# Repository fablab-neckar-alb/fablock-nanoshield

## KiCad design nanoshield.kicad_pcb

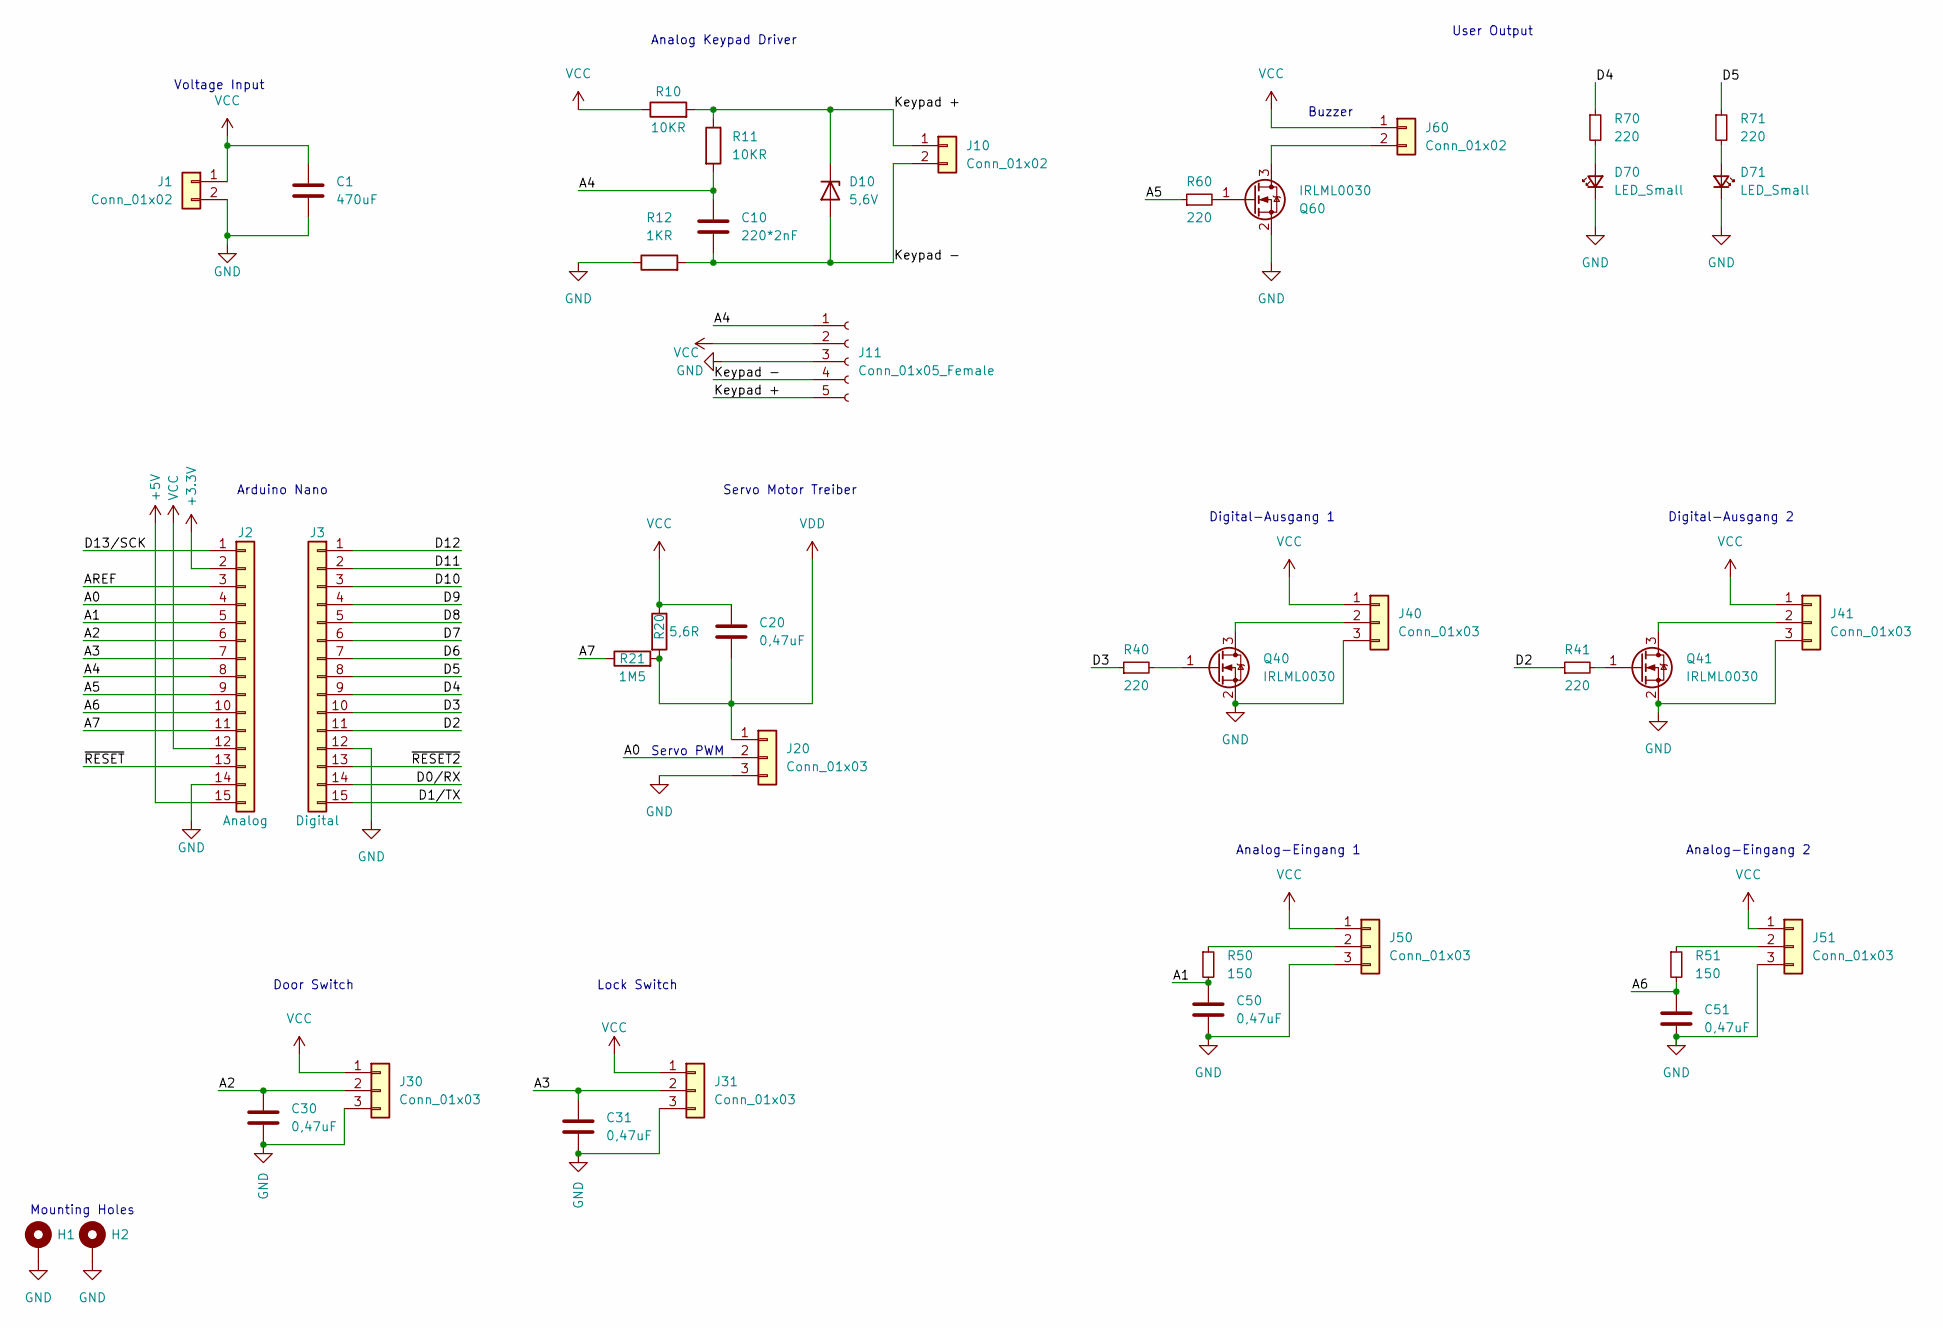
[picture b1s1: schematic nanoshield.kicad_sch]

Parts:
C1: 470uF; CP_Radial_D10.0mm_P5.00mm
C10: 220*2nF; C_Rect_L7.2mm_W2.5mm_P5.00mm_FKS2_FKP2_MKS2_MKP2
C20, C30, C31, C50, C51: 0,47uF; C_Rect_L7.2mm_W3.0mm_P5.00mm_FKS2_FKP2_MKS2_MKP2
D10: 5,6V; D_DO-15_P12.70mm_Horizontal
D70, D71: LED_Small; LED_Rectangular_W3.0mm_H2.0mm
H1: H1; MountingHole_3.5mm_Pad
H2: H2; MountingHole_3.5mm_Pad
J1, J10, J60: Conn_01x02; PhoenixContact_MCV_1,5_2-G-3.5_1x02_P3.50mm_Vertical
J2: Analog; PinHeader_1x15_P2.54mm_Vertical
J3: Digital; PinHeader_1x15_P2.54mm_Vertical
J11: Conn_01x05_Female; PinSocket_1x05_P2.54mm_Vertical
J20, J30, J31, J40, J41, J50, J51: Conn_01x03; PhoenixContact_MCV_1,5_3-G-3.5_1x03_P3.50mm_Vertical
Q40, Q41, Q60: IRLML0030; SOT-23
R10, R11: 10KR; R_Axial_DIN0309_L9.0mm_D3.2mm_P12.70mm_Horizontal
R12: 1KR; R_Axial_DIN0309_L9.0mm_D3.2mm_P12.70mm_Horizontal
R20: 5,6R; R_Axial_DIN0411_L9.9mm_D3.6mm_P20.32mm_Horizontal
R21: 1M5; R_Axial_DIN0309_L9.0mm_D3.2mm_P12.70mm_Horizontal
R40, R41, R60, R70, R71: 220; R_Axial_DIN0309_L9.0mm_D3.2mm_P12.70mm_Horizontal
R50, R51: 150; R_Axial_DIN0309_L9.0mm_D3.2mm_P12.70mm_Horizontal

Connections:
+3V3: J2.2
+5V: J2.15
/A0: J2.4, J20.2
/A1: C50.1, J2.5, R50.2
/A2: C30.1, J2.6, J30.2
/A3: C31.1, J2.7, J31.2
/A4: C10.1, J2.8, J11.1, R11.2
/A5: J2.9, R60.1
/A6: C51.1, J2.10, R51.2
/A7: J2.11, R21.1
/AREF: J2.3
/D0/RX: J3.14
/D1/TX: J3.15
/D2: J3.11, R41.1
/D3: J3.10, R40.1
/D4: J3.9, R70.1
/D5: J3.8, R71.1
/D6: J3.7
/D7: J3.6
/D8: J3.5
/D9: J3.4
/D10: J3.3
/D11: J3.2
/D12: J3.1
/D13/SCK: J2.1
/Keypad +: D10.1 (K), J10.1, J11.5, R10.2, R11.1
/Keypad -: C10.2, D10.2 (A), J10.2, J11.4, R12.2
/~RESET2: J3.13
/~RESET: J2.13
GND: C1.2, C30.2, C31.2, C50.2, C51.2, D70.1 (K), D71.1 (K), H1.1, H2.1, J1.2, J2.14, J3.12, J11.3, J20.3, J30.3, J31.3, J40.3, J41.3, J50.3, J51.3, Q40.2 (S), Q41.2 (S), Q60.2 (S), R12.1
unnamed: D70.2 (A), R70.2
unnamed: D71.2 (A), R71.2
unnamed: J40.2, Q40.3 (D)
unnamed: J41.2, Q41.3 (D)
unnamed: J50.2, R50.1
unnamed: J51.2, R51.1
unnamed: J60.2, Q60.3 (D)
unnamed: Q40.1 (G), R40.2
unnamed: Q41.1 (G), R41.2
unnamed: Q60.1 (G), R60.2
VCC: C1.1, C20.1, J1.1, J2.12, J11.2, J30.1, J31.1, J40.1, J41.1, J50.1, J51.1, J60.1, R10.1, R20.1
VDD: C20.2, J20.1, R20.2, R21.2

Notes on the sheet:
Analog-Eingang 2
Digital-Ausgang 1
Digital-Ausgang 2
Voltage Input
Analog-Eingang 1
Arduino Nano
User Output
Servo Motor Treiber
Analog Keypad Driver
Servo PWM
Door Switch
Buzzer
Mounting Holes
Lock Switch

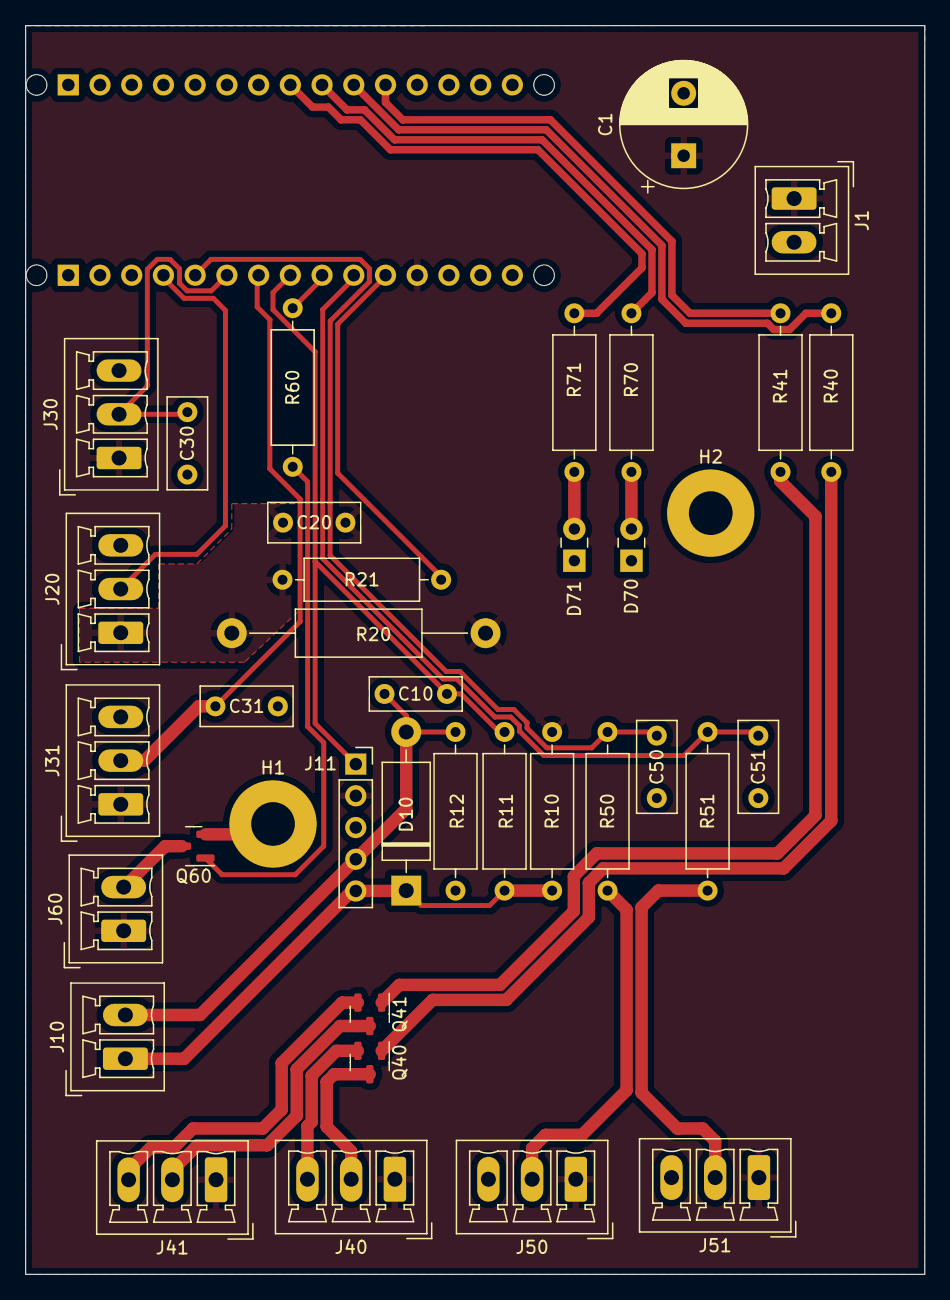
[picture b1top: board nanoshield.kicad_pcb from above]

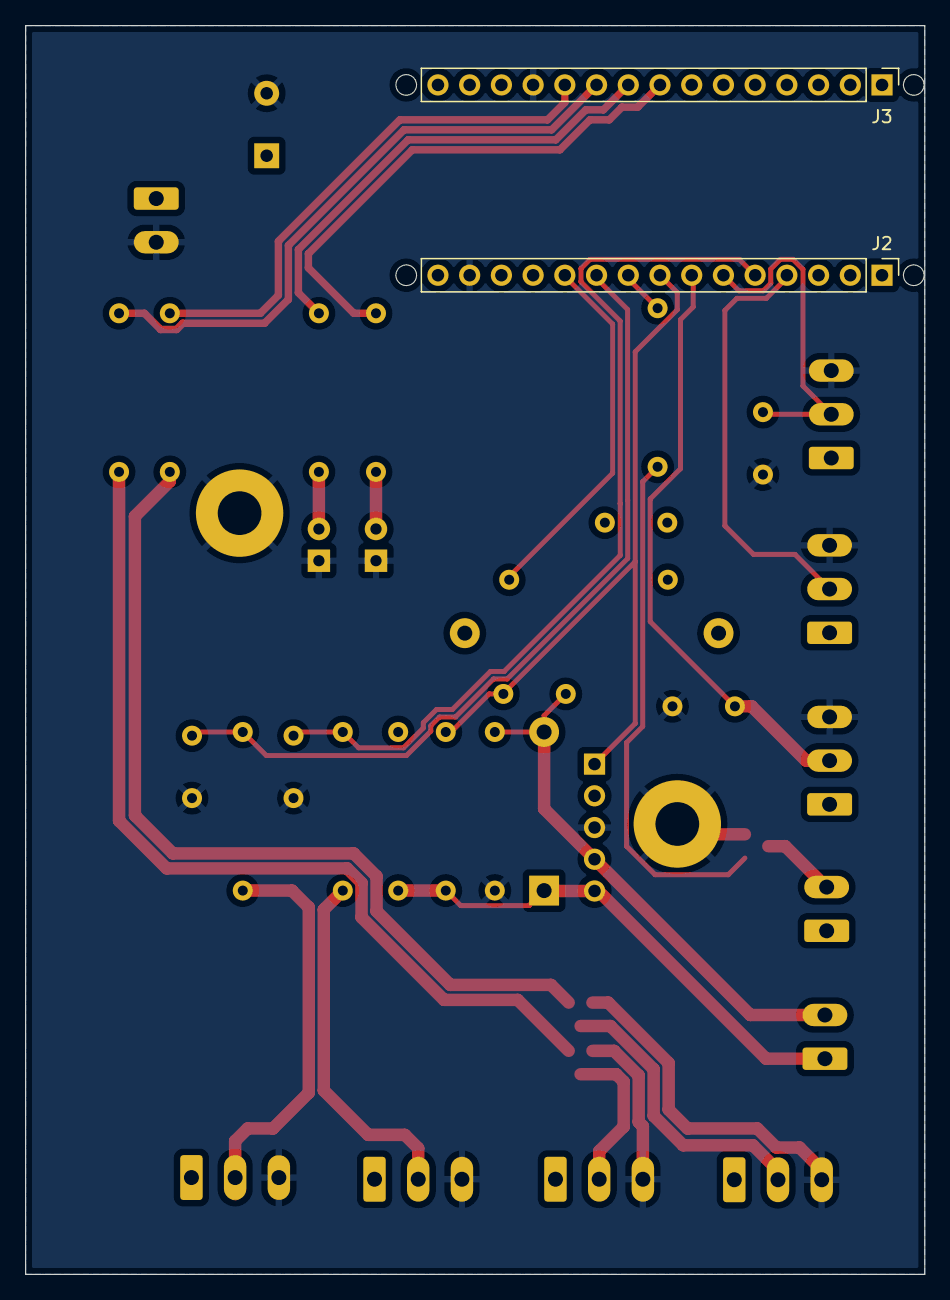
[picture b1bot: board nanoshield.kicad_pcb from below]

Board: 2 copper layers, 72.0 x 100.0 mm, 44 parts (2 on the bottom side), 27 nets.

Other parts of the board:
MH1, MH2, MH3, MH4: MountingHole_65mil

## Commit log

2023-04-25 Version 1
2023-08-08 Added Pages
